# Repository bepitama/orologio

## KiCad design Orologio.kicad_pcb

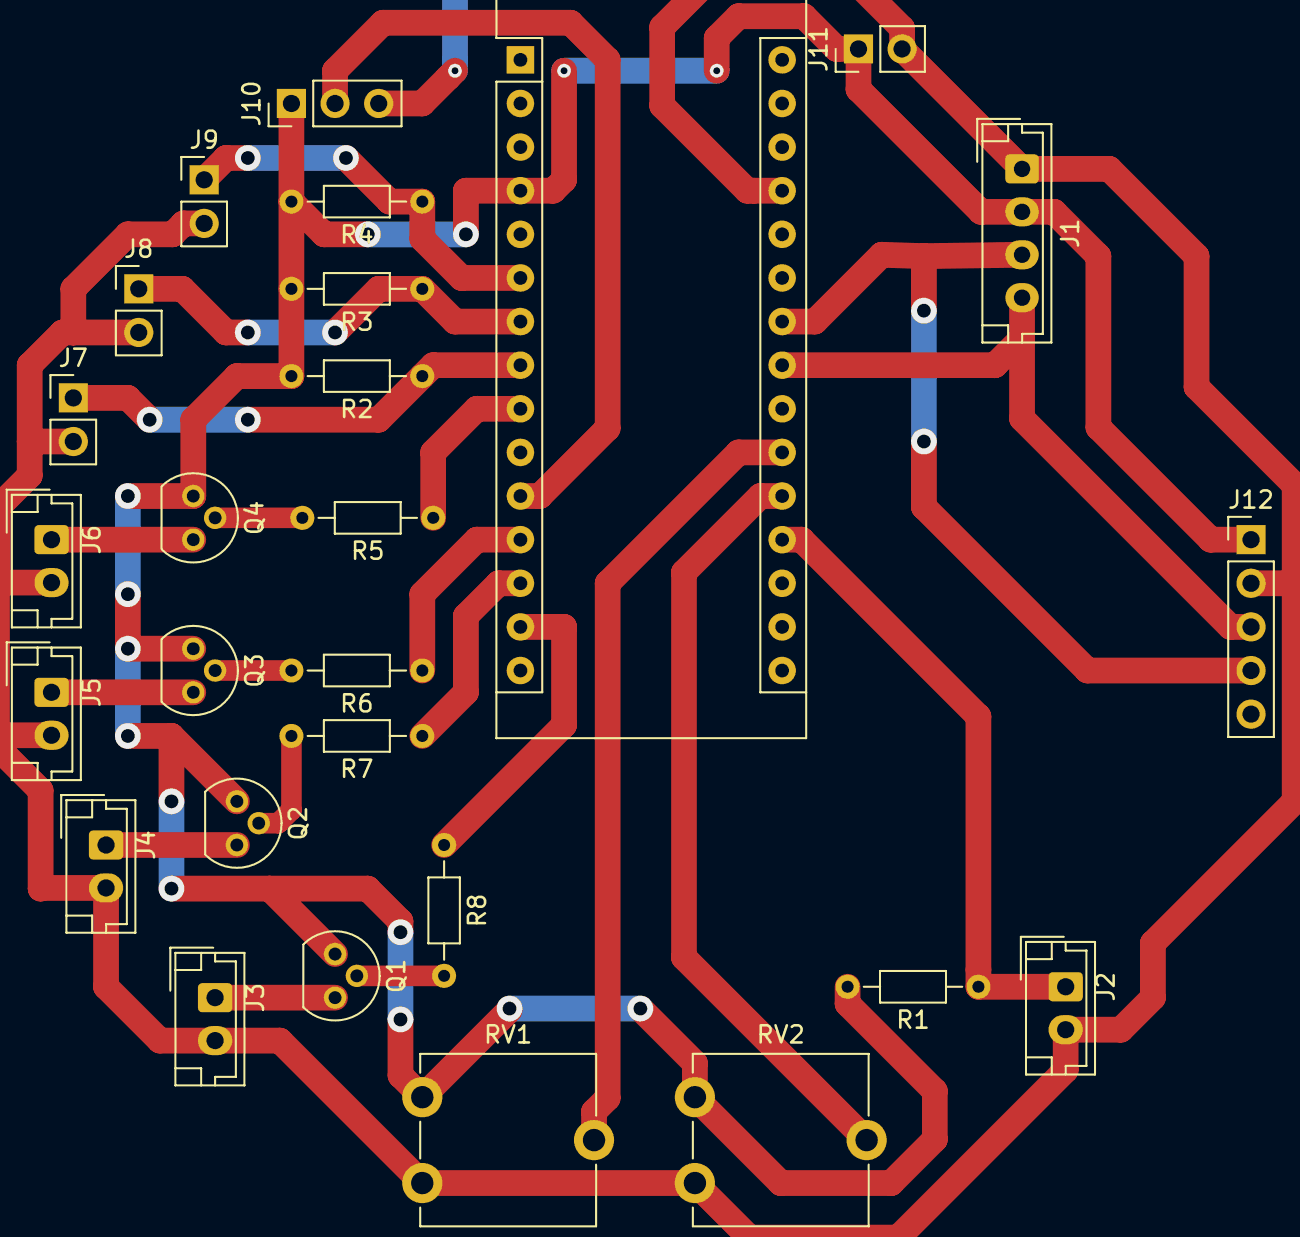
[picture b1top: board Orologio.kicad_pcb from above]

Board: 2 copper layers, 27 parts (0 on the bottom side), 23 nets.

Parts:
A1: Arduino_Nano_v3.x; Arduino_Nano
J1: BME280; JST_EH_B4B-EH-A_1x04_P2.50mm_Vertical
J2: Photoresistor; JST_EH_B2B-EH-A_1x02_P2.50mm_Vertical
J3: LED4; JST_EH_B2B-EH-A_1x02_P2.50mm_Vertical
J4: LED3; JST_EH_B2B-EH-A_1x02_P2.50mm_Vertical
J5: LED2; JST_EH_B2B-EH-A_1x02_P2.50mm_Vertical
J6: LED1; JST_EH_B2B-EH-A_1x02_P2.50mm_Vertical
J7: BUT3; PinHeader_1x02_P2.54mm_Vertical
J8: BUT2; PinHeader_1x02_P2.54mm_Vertical
J9: BUT1; PinHeader_1x02_P2.54mm_Vertical
J10: WS2812; PinHeader_1x03_P2.54mm_Vertical
J11: Power; PinHeader_1x02_P2.54mm_Vertical
J12: RTC; PinHeader_1x05_P2.54mm_Vertical
Q1, Q2, Q3, Q4: 2N2219; TO-92
R1: 100K; R_Axial_DIN0204_L3.6mm_D1.6mm_P7.62mm_Horizontal
R2, R3, R4: 10K; R_Axial_DIN0204_L3.6mm_D1.6mm_P7.62mm_Horizontal
R5, R6, R7, R8: 1000; R_Axial_DIN0204_L3.6mm_D1.6mm_P7.62mm_Horizontal
RV1, RV2: R_POT; Potentiometer_ACP_CA9-V10_Vertical

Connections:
unnamed: A1.4, J1.2, J10.1, J11.1, J12.1, Q1.1, Q2.1, Q3.1, Q4.1, R1.2, R2.2, R3.2, R4.2, RV1.3, RV2.3
unnamed: A1.6, J9.1, R4.1
unnamed: A1.7, J8.1, R3.1
unnamed: A1.8, J7.1, R2.1
unnamed: A1.9, R5.1
unnamed: A1.11, J10.2
unnamed: A1.12, R6.1
unnamed: A1.13, R7.1
unnamed: A1.14, R8.1
unnamed: A1.19, J2.1, R1.1
unnamed: A1.20, RV2.2
unnamed: A1.21, RV1.2
unnamed: A1.23, J1.4, J12.3
unnamed: A1.24, J1.3, J12.4
unnamed: A1.27, J1.1, J2.2, J3.2, J4.2, J5.2, J6.2, J7.2, J8.2, J9.2, J10.3, J11.2, J12.2, RV1.1, RV2.1
unnamed: J3.1, Q1.3
unnamed: J4.1, Q2.3
unnamed: J5.1, Q3.3
unnamed: J6.1, Q4.3
unnamed: Q1.2, R8.2
unnamed: Q2.2, R7.2
unnamed: Q3.2, R6.2
unnamed: Q4.2, R5.2

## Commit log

2020-06-13 Create LICENSE
